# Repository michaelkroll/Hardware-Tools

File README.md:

Hardware-Tools
==============

Hardware tools I created during development of my hardware designs.

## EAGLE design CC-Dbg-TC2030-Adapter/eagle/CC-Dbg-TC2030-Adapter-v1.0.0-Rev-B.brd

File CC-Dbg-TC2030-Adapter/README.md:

CC-Debugger TC2030 Adapter
===

The CC-Debugger TC2030 Adapter was created in order to reduce the space and cost to program the firmware of my BLEbee. The header I was using on the BLE-Shield was too big to be used on the BLEbee, but an additional cable and the adapter is necessary.

In order to bulid the module, order the PCB at http://www.oshpark.com (http://www.oshpark.com/shared_projects/Ff2LiKQA) and add some headers to the board
 
Photos
===

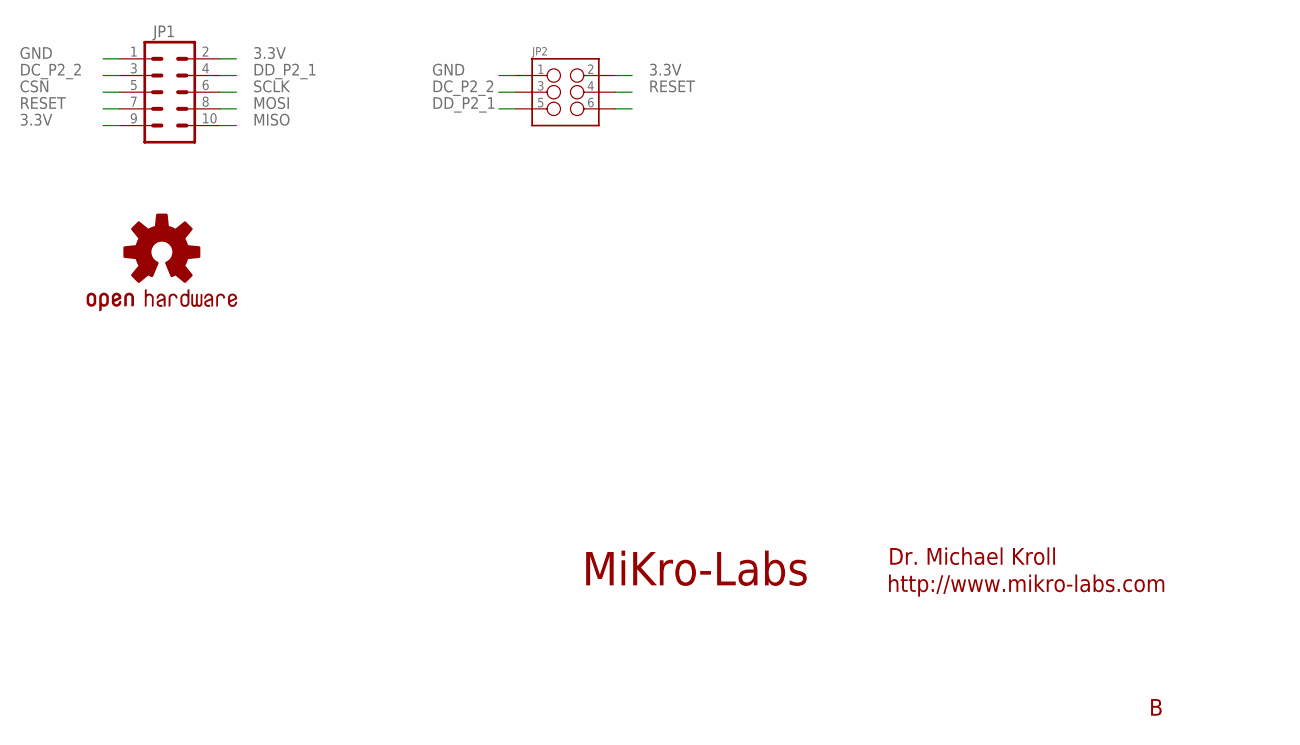
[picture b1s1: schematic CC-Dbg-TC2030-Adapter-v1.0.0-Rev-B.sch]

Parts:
JP1: M05X2SHD; 2X5-SHROUDED
JP2: M03X2; 2X3-SHROUDED
LOGO1: OSHW-LOGOS; OSHW-LOGO-S

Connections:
3.3V: JP1.2, JP1.9, JP2.2
CSN: JP1.5
DC_P2_2: JP1.3, JP2.3
DD_P2_1: JP1.4, JP2.5
GND: JP1.1, JP2.1
MISO: JP1.10
MOSI: JP1.8
RESET: JP1.7, JP2.4
SCLK: JP1.6

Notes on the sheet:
Dr. Michael Kroll
MiKro-Labs
http://www.mikro-labs.com

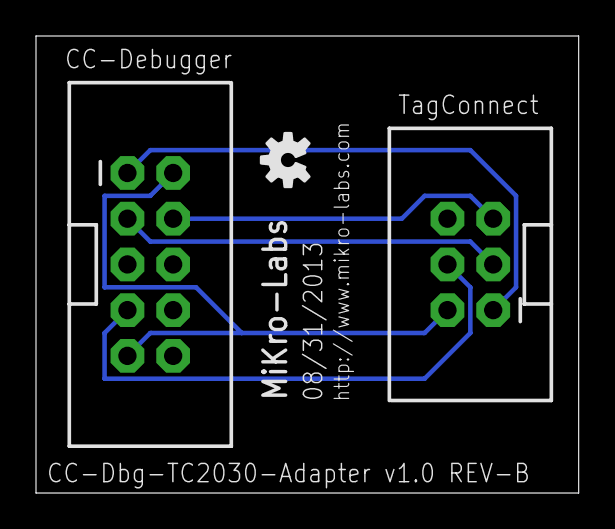
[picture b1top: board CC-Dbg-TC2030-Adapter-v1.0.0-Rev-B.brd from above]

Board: 2 copper layers, 30.1 x 25.4 mm, 3 parts (0 on the bottom side), 5 nets.

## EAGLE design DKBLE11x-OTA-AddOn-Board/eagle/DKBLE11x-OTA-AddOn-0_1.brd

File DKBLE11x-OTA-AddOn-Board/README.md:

DKBLE11x OTA Add On Board
===

The DKBLE11x OTA Add On Board was created to test the OTA firmware update feature introduced in Bluegiga's SDK1.2.2 build 100 for the BLE112 and BLE113 Bluetooth Smart Module.

In order to bulid the module, order the PCB at http://www.oshpark.com (http://www.oshpark.com/shared_projects/nWPpYei9) and a few parts e.g. from digikey:

 - 1 x 1uF capacitor in 0603 package
 - 2 x 10k resistor in 0603 package
 - 1 x SPI Flash W25X20CLSNIG-ND Digikey part number: W25X20CLSNIG-ND
 - 2 x 8 pin Arduino headers (https://www.sparkfun.com/products/11895)
 
Photos
===

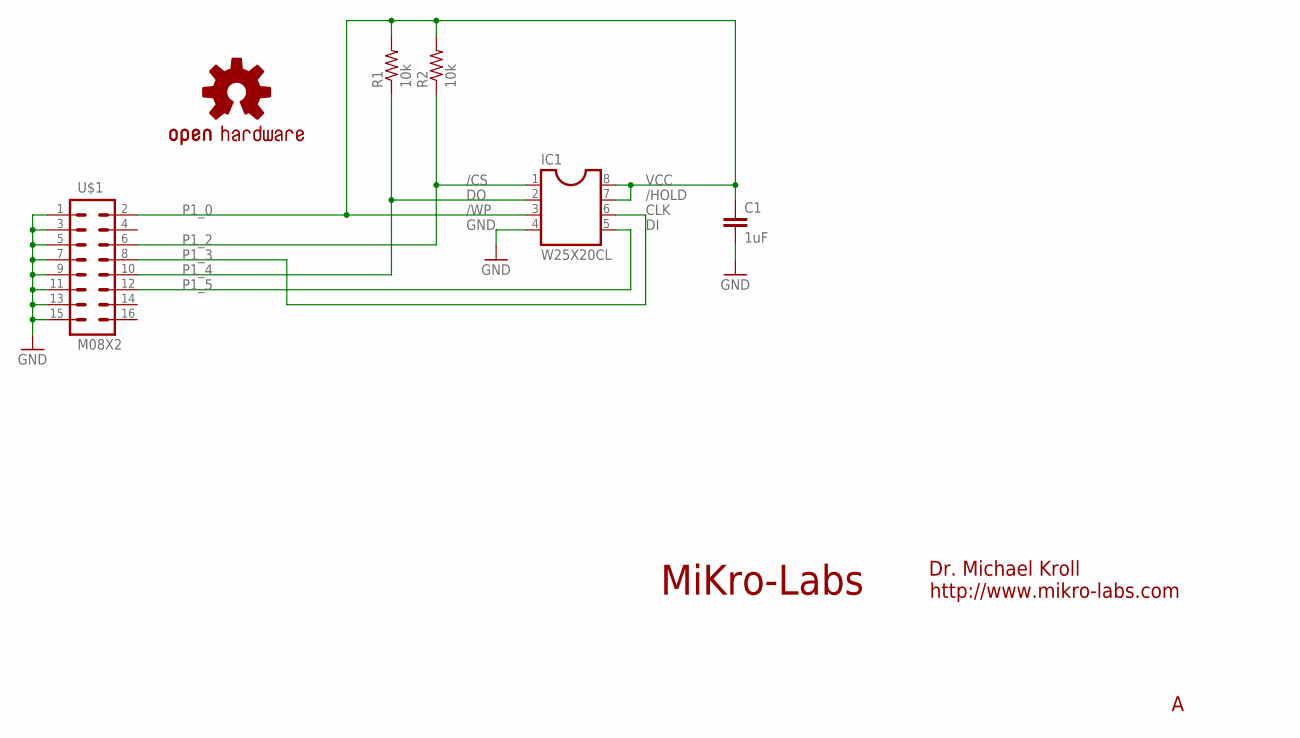
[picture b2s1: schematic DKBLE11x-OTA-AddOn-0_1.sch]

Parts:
C1: 1uF; 0603-CAP
IC1: W25X20CL; SO-8
LOGO1: OSHW-LOGOS; OSHW-LOGO-S
R1, R2: 10k; 0603-RES
U$1: M08X2; 2X8

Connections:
/HOLD: C1.1, IC1.3, IC1.7, IC1.8, R1.2, R2.2, U$1.2
CLK: IC1.6, U$1.8
DI: IC1.5, U$1.12
DO: IC1.2, R1.1, U$1.10
GND: C1.2, IC1.4, U$1.1, U$1.3, U$1.5, U$1.7, U$1.9, U$1.11, U$1.13, U$1.15
P1_2: IC1.1, R2.1, U$1.6

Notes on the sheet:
P1_0
P1_2
P1_3
P1_4
P1_5
VCC
/HOLD
CLK
GND
/WP
/CS
MiKro-Labs
http://www.mikro-labs.com
Dr. Michael Kroll

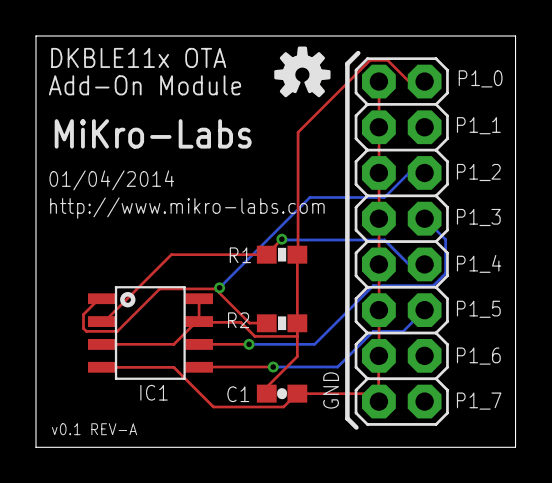
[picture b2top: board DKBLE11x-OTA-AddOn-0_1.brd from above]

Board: 4 copper layers, 26.6 x 22.9 mm, 6 parts (0 on the bottom side), 6 nets.

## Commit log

2014-04-06 v0.1 of the DKBLE11x OTA AddOn board comitted.
2014-04-06 Photos added.
2014-04-06 size changed.
2014-05-18 CC-Debugger TagConnect 2030 Adapter added.
2014-05-18 changed the images to JPG.

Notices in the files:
parts and their libraries:
SparkFun-Aesthetics: Licensing: CC v3.0 Share-Alike You are welcome to use this library for commercial purposes.
